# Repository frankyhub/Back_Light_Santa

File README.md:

<div align="center">

|[:skull:ISSUE](https://github.com/frankyhub/Back_Light_Santa/issues?q=is%3Aissue)|[:speech_balloon: Forum /Discussion](https://github.com/frankyhub/Back_Light_Santa/discussions)|[:grey_question:WiKi](https://github.com/frankyhub/Back_Light_Santa/wiki)||
|--|--|--|--|
| | | | |
<a href="https://github.com/frankyhub/Back_Light_Santa/issues">|<a href="https://github.com/frankyhub/Back_Light_Santa/discussions">|<a href="https://github.com/frankyhub/Back_Light_Santa/6eleases">||
|| <a href="https://github.com/frankyhub/Back_Light_Santa/pulse" alt="Activity">| <a href="https://github.com/frankyhub/Back_Light_Santa/graphs/traffic">  |<a href="https://github.com/frankyhub?tab=stars"> ||

<br> <br>

## BOM

| Anzahl | Bezeichnung | 
| -------- | -------- | 
| 1  |  Platine	  |
|  1 | Batteriehalter	   |
| 1  | CR2032	   |
| 1  |  Schalter  |
| 1  |  R1	100  |
|  4 |   D1 - D4	LED 5mm|  
| -------- | -------- | 

---

<div style="position:absolute; left:2cm; ">   
<ol class="breadcrumb" style="border-top: 2px solid black;border-bottom:2px solid black; height: 45px; width: 900px;"> <p align="center"><a href="#oben">nach oben</a></p></ol>
</div>  

---

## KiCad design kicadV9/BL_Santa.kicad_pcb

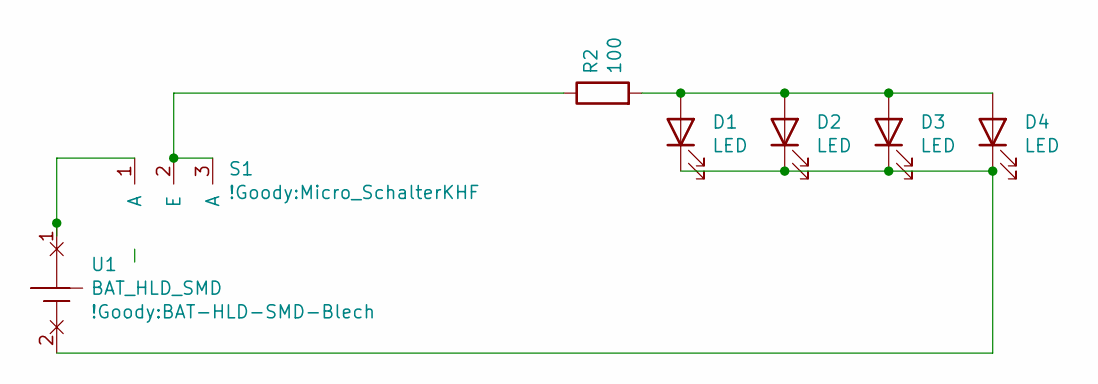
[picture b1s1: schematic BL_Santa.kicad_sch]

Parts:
D1, D2, D4: LED; LED_D5.0mm
D3: LED; LED_D4.0mm
R2: 100; R_Axial_DIN0207_L6.3mm_D2.5mm_P10.16mm_Horizontal
S1: Micro_Schalter; Micro_SchalterKHF
U1: BAT_HLD_SMD; BAT-HLD-SMD-Blech

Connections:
unnamed: D1.2 (A), D2.2 (A), D3.2 (A), D4.2 (A), R2.2
unnamed: D1.1 (K), D2.1 (K), D3.1 (K), D4.1 (K), U1.2
unnamed: S1.1 (A), U1.1
unnamed: R2.1, S1.2 (E), S1.3 (A)

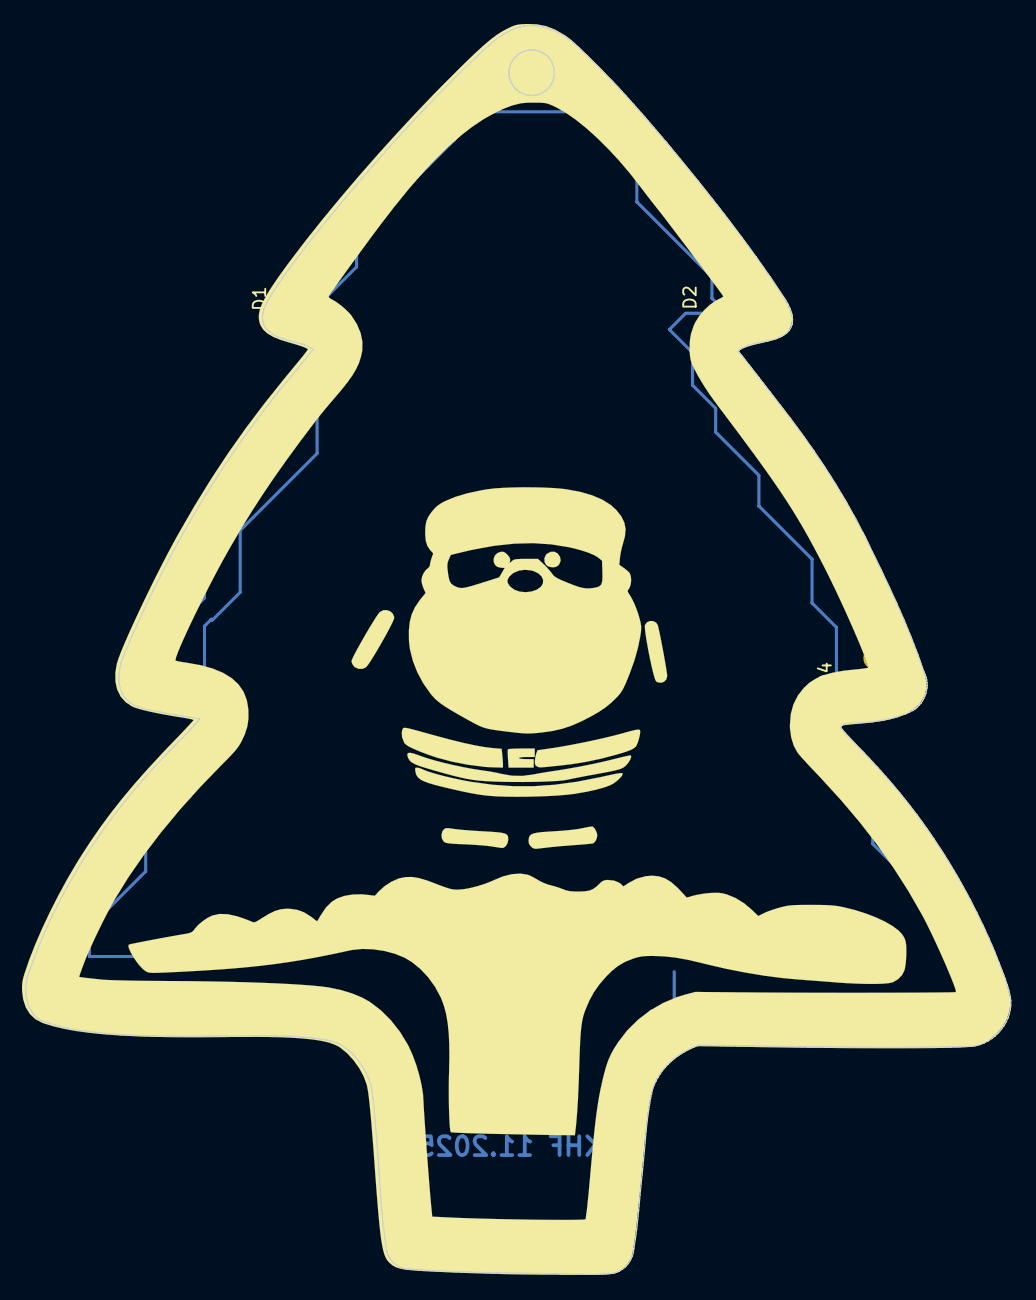
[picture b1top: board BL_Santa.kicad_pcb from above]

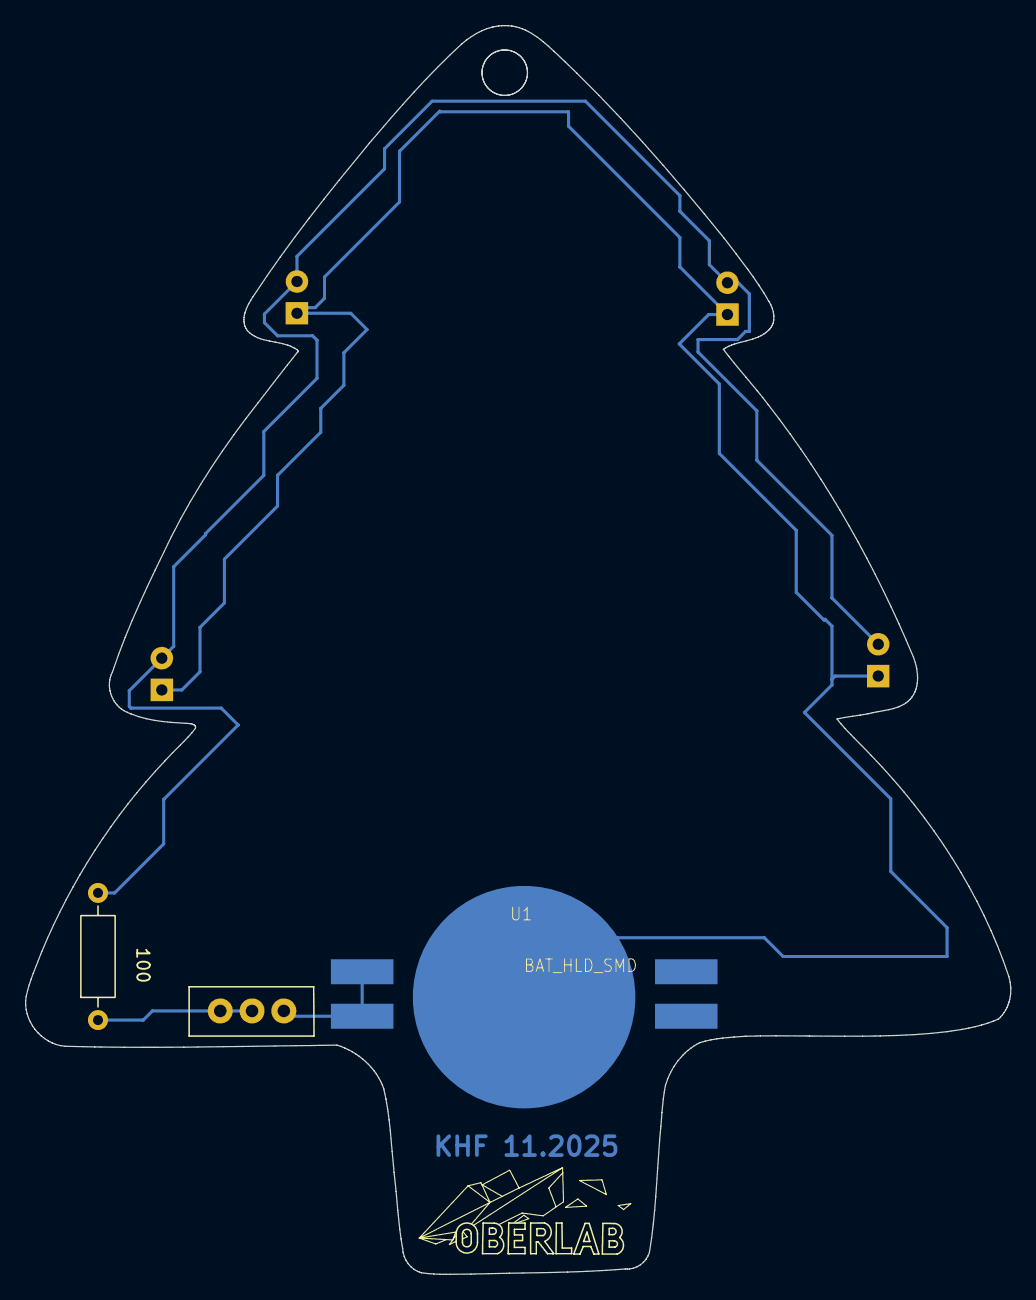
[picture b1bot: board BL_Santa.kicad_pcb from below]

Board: 2 copper layers, 78.7 x 99.8 mm, 7 parts (3 on the bottom side), 4 nets.

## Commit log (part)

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2025-11-21 V21112025
2025-12-01 V01122025
2025-12-01 V01122025
    Updated image and badge links in README.
